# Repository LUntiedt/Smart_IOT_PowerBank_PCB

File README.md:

# Smart IoT Power Bank — Hardware (PD Edition)

A bidirectional USB-C Power Delivery (PD) power bank built around a software-defined PD stack and an I²C buck-boost charger. This repository holds the **KiCad hardware design** (schematic, layout, BOM, fabrication outputs). The firmware lives in a separate repository.

> **Firmware:** [`smart-iot-power-bank-firmware`](#) 

---

<!-- ───────────────────────────────────────────────────────────── -->
<!-- PROJECT IMAGE — replace the placeholder below with a real photo -->
<!-- Suggested: top-down render or photo of the assembled PCB.       -->
<!-- Drop the file into docs/img/ and update the path.               -->
<!-- ───────────────────────────────────────────────────────────── -->

<p align="center">
  
  <br>
  <em>Smart IoT Power Bank</em>
</p>

---

## 1. Overview

The board implements a professional power-management architecture comparable to those found in modern laptops. The same USB-C port handles **input (sink)** and **output (source/OTG)**, limited to a robust **30 W**. Energetic characterization (V/I telemetry, efficiency) is done entirely with the **internal 16-bit ADCs of the charge controller**, avoiding external sense amplifiers.

| Property | Value |
| :--- | :--- |
| Topology | Bidirectional USB-C PD (sink + source) |
| Battery | 4S1P Li-ion, 14.8 V nominal (~45 Wh) with integrated protection BMS |
| Max power | 30 W (5 V / 9 V / 12 V / 15 V / 20 V profiles) |
| MCU | ESP32-C3 (Wi-Fi/BLE) |
| Charger | TI BQ25792 I²C buck-boost |
| PD PHY | onsemi FUSB302B |
| Logic rail | TPS54202 buck → 3.3 V |
| EDA tool | KiCad |
| Fab house | [Aisler](https://aisler.net) (stackup & design rules tuned to Aisler) |

---

## 2. Hardware Architecture

### A. Power Path & USB-C Communication

| Designator | Part | Function | System Role |
| :--- | :--- | :--- | :--- |
| **U3** | `BQ25792RQMR` (TI) | I²C buck-boost charger | Handles charging (buck) and discharging (OTG/boost) in hardware. Single inductor L1 (2.2 µH). |
| **U1** | `FUSB302B11MPX` (onsemi) | USB Type-C PD PHY | Monitors the CC pins and translates PD signalling into I²C messages for the MCU. |
| **U6** | `TPS54202HDDCR` (TI) | 2 A step-down | Generates a clean **3.3 V** logic rail from the fluctuating system voltage. Inductor L2 (10 µH). |
| **Q1, Q2** | `CSD17581Q3A` (TI) | Dual N-channel MOSFETs | Back-to-back FETs for **reverse-polarity protection** / VBUS load isolation; block reverse current from the USB port into the system. |
| **J2** | Würth WR-MPC4 `64900311122` | Battery connector | Connects the external **4S1P 18650 pack** (14.8 V, ~45 Wh, with internal BMS). |

### B. Protection (TVS / ESD / Clamps)

| Designator | Part | Function | Notes |
| :--- | :--- | :--- | :--- |
| **U2, U4** | `TVS2200DRVR` (TI) | Flat-clamp surge protection | **VBUS TVS** — tight clamping on the high-current bus. |
| **D2, D4** | `TPD4E05U06DQAR` (TI) | 4-channel low-cap ESD | Protects **CC lines and the differential pairs** without loading the high-speed signals. |
| **D1** | `ZLLS350` (Diodes Inc.) | 40 V Schottky | Power-path / bootstrap diode. |
| **Z1** | `MMSZ5242B` | 12 V Zener | Rail clamp. |

### C. Sensing & Intelligence (IoT layer)

| Designator | Part | Function | Engineering benefit |
| :--- | :--- | :--- | :--- |
| **U5** | `ESP32-C3-WROOM-02-H4` (Espressif) | Master MCU | FSM control, software PD stack, I²C master, BLE server. |
| — | BQ25792 (internal) | 16-bit ADC telemetry | Reads V_BUS, I_BUS, V_BAT, I_BAT from the charger — no external current sensors. |
| **(TS pin)** | 10 k NTC | Thermistor | Cell temperature monitoring via the BQ25792 TS pin. |
| **J5** | 1×04 header | OLED / I²C | 0.96" OLED for local PD-profile and efficiency readout. |

### D. Connectors, Switches, Indicators

| Designator | Part | Function |
| :--- | :--- | :--- |
| **J1, J3** | USB-C receptacle (Würth `629722000214`) | Two USB-C ports — see differential-pair routing below. |
| **J4** | 2×03 header | Programming / debug header. |
| **SW1, SW2** | Würth tactile `434121025816` | Boot / reset buttons. |
| **D3** | Green LED (Würth) | Status indication. |

> Full part list with manufacturer numbers, footprints and datasheets: **[`ESP_Smart_IoT_Power_Bank.csv`](ESP_Smart_IoT_Power_Bank.csv)**.

---

## 3. Engineering Features & Physics

### I. Cascaded Power Supply (Logic Isolation)

To avoid system reboots under heavy load, the supply is cascaded:

1. **Primary stage** — the BQ25792 generates the system rail `V_SYS` from the 4S pack.
2. **Secondary stage** — a dedicated **TPS54202** bucks `V_SYS` down to a constant **3.3 V** for the logic. The ESP32 therefore always sees a clean rail, independent of current spikes in the power stage.

### II. Efficient 4S Power Routing (Buck & OTG)

The 4S pack (14.8 V) minimizes conversion losses:

* **Buck mode (sink):** at 20 V input the IC acts as an efficient step-down.
* **Buck/boost mode (source):** in OTG, 5 V / 9 V / 12 V are produced highly efficiently by buck conversion; only 20 V profiles (e.g. laptops) require a slight boost.

### III. Thermal & Electrical Derating

Thanks to the 4S configuration, PCB currents stay **below 3 A** even at 30 W:

```
I_bat_max = P_out / (U_bat · η)
I_bat_max = 30 W / (12.0 V · 0.9) ≈ 2.7 A   (worst case, empty pack)
```

On overheat (NTC > 60 °C) the ESP32 throttles PD power via software re-negotiation down to **5 W (5 V / 1 A)** as a fallback.

---

## 4. PCB Stackup & Layout

**4-layer board, built to Aisler's stackup and design rules.**

| Layer | Role |
| :--- | :--- |
| **Top** | Power / Signal |
| **Inner 1** | GND |
| **Inner 2** | GND |
| **Bottom** | Power / Signal |

The dual inner ground planes give the high-speed pairs a continuous reference and a low-impedance return for the power stage.

### Differential pairs

Two **impedance-controlled 90 Ω differential pairs** (USB 2.0 spec):

1. **USB power port (BQ25792):** backwards-compatible USB data for the power path.
2. **Debug/flash port (ESP32-C3):** USB used to flash and debug the MCU.

Both pairs are protected by the low-capacitance `TPD4E05U06` ESD arrays so the added capacitance does not degrade signal integrity.

### Layout guidelines

* **Ground partitioning** — clean ground concept separating the power stage (BQ25792) from the logic (ESP32 / TPS54202).
* **Copper polygons** — power paths (V_BUS, V_BAT, V_SYS) routed as filled polygons.
* **Thermal management** — implemented high power rails on both sides of the board to increase thermal capacity and placing a generous amount of vias to distribute current evenly

---

## 5. Design Decisions Log

* **Dual-MOSFET reverse-polarity protection** (Q1/Q2, CSD17581Q3A) instead of a single series diode — near-zero conduction loss on the power path.
* **VBUS TVS** (TVS2200) for surge clamping on the high-current bus.
* **Low-capacitance TVS/ESD** (TPD4E05U06) on CC lines and the differential pairs to preserve signal integrity.
* **Two 90 Ω impedance-controlled diff pairs:** one for backwards-compatible USB power data (BQ), one dedicated to flashing/debugging the MCU.
* **Aisler** chosen as fab house — the stackup and design rules in this project are tuned to Aisler's process.

---

## 6. Status

Hardware design in KiCad. See the firmware repository for the FreeRTOS PD stack.

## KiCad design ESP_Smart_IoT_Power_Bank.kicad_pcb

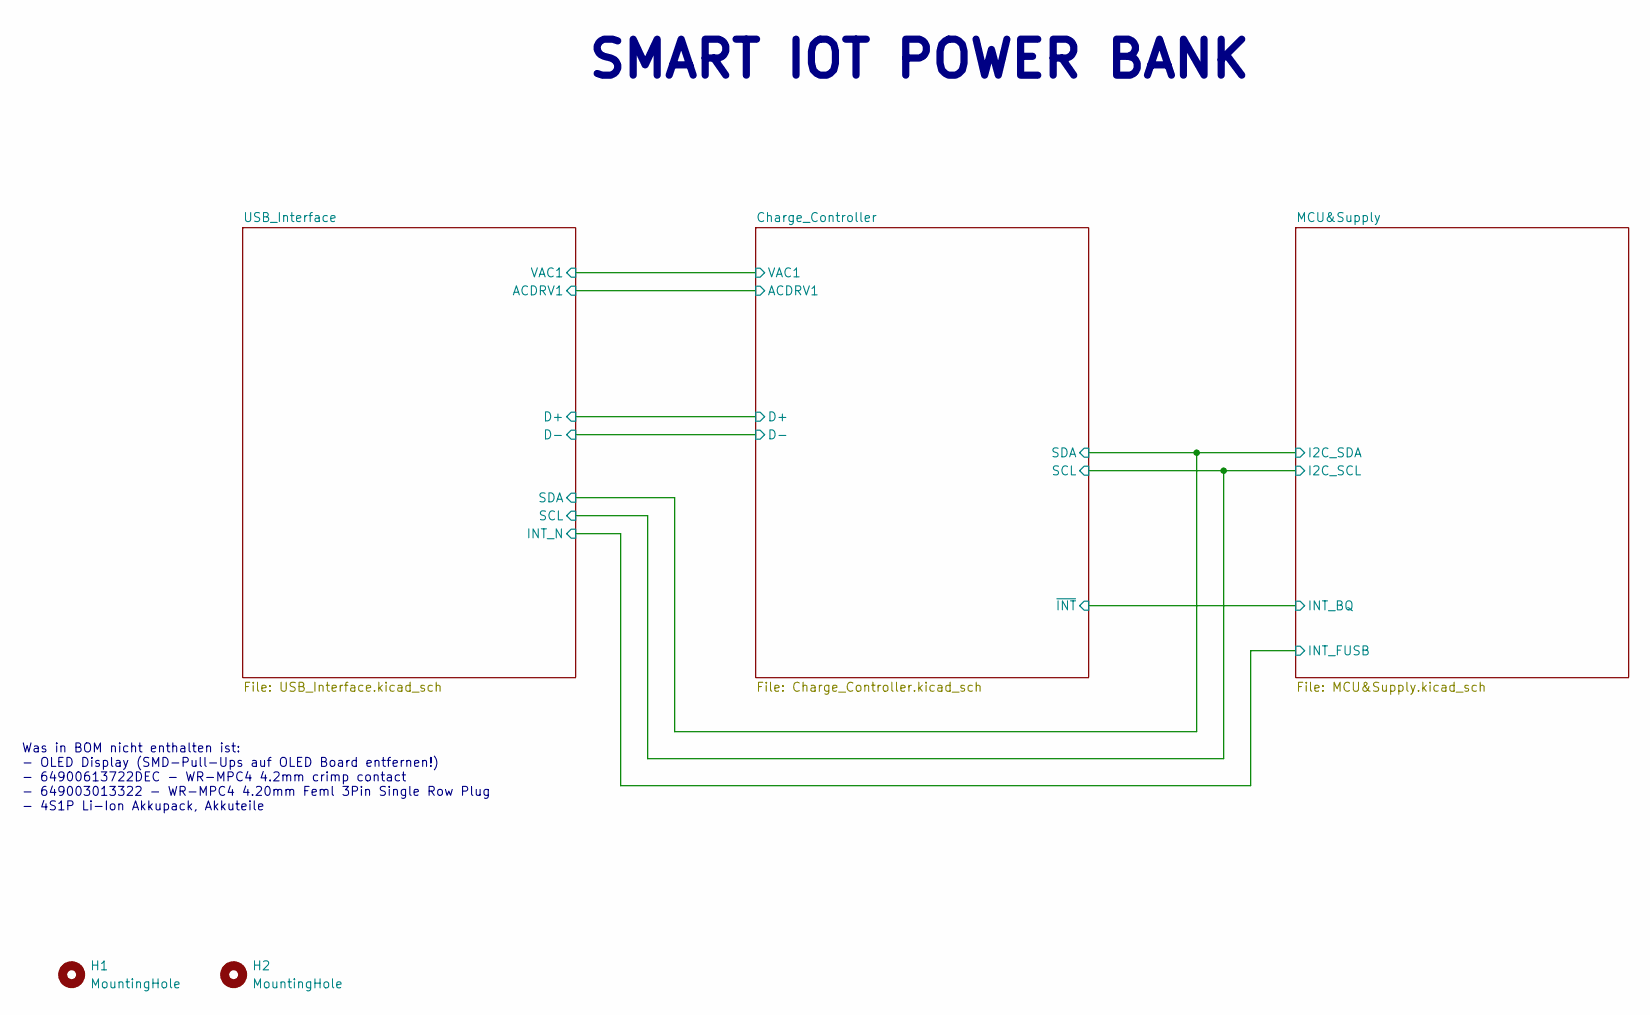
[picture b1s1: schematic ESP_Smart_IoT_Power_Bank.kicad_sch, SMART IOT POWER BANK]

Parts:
H1, H2: MountingHole; MountingHole_3.2mm_M3_ISO14580

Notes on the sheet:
SMART IOT POWER BANK
Was in BOM nicht enthalten ist: - OLED Display (SMD-Pull-Ups auf OLED Board entfernen!) - 64900613722DEC - WR-MPC4 4.2mm crimp contact - 649003013322 - WR-MPC4 4.20mm Feml 3Pin Single Row Plug - 4S1P Li-Ion Akkupack, Akkuteile

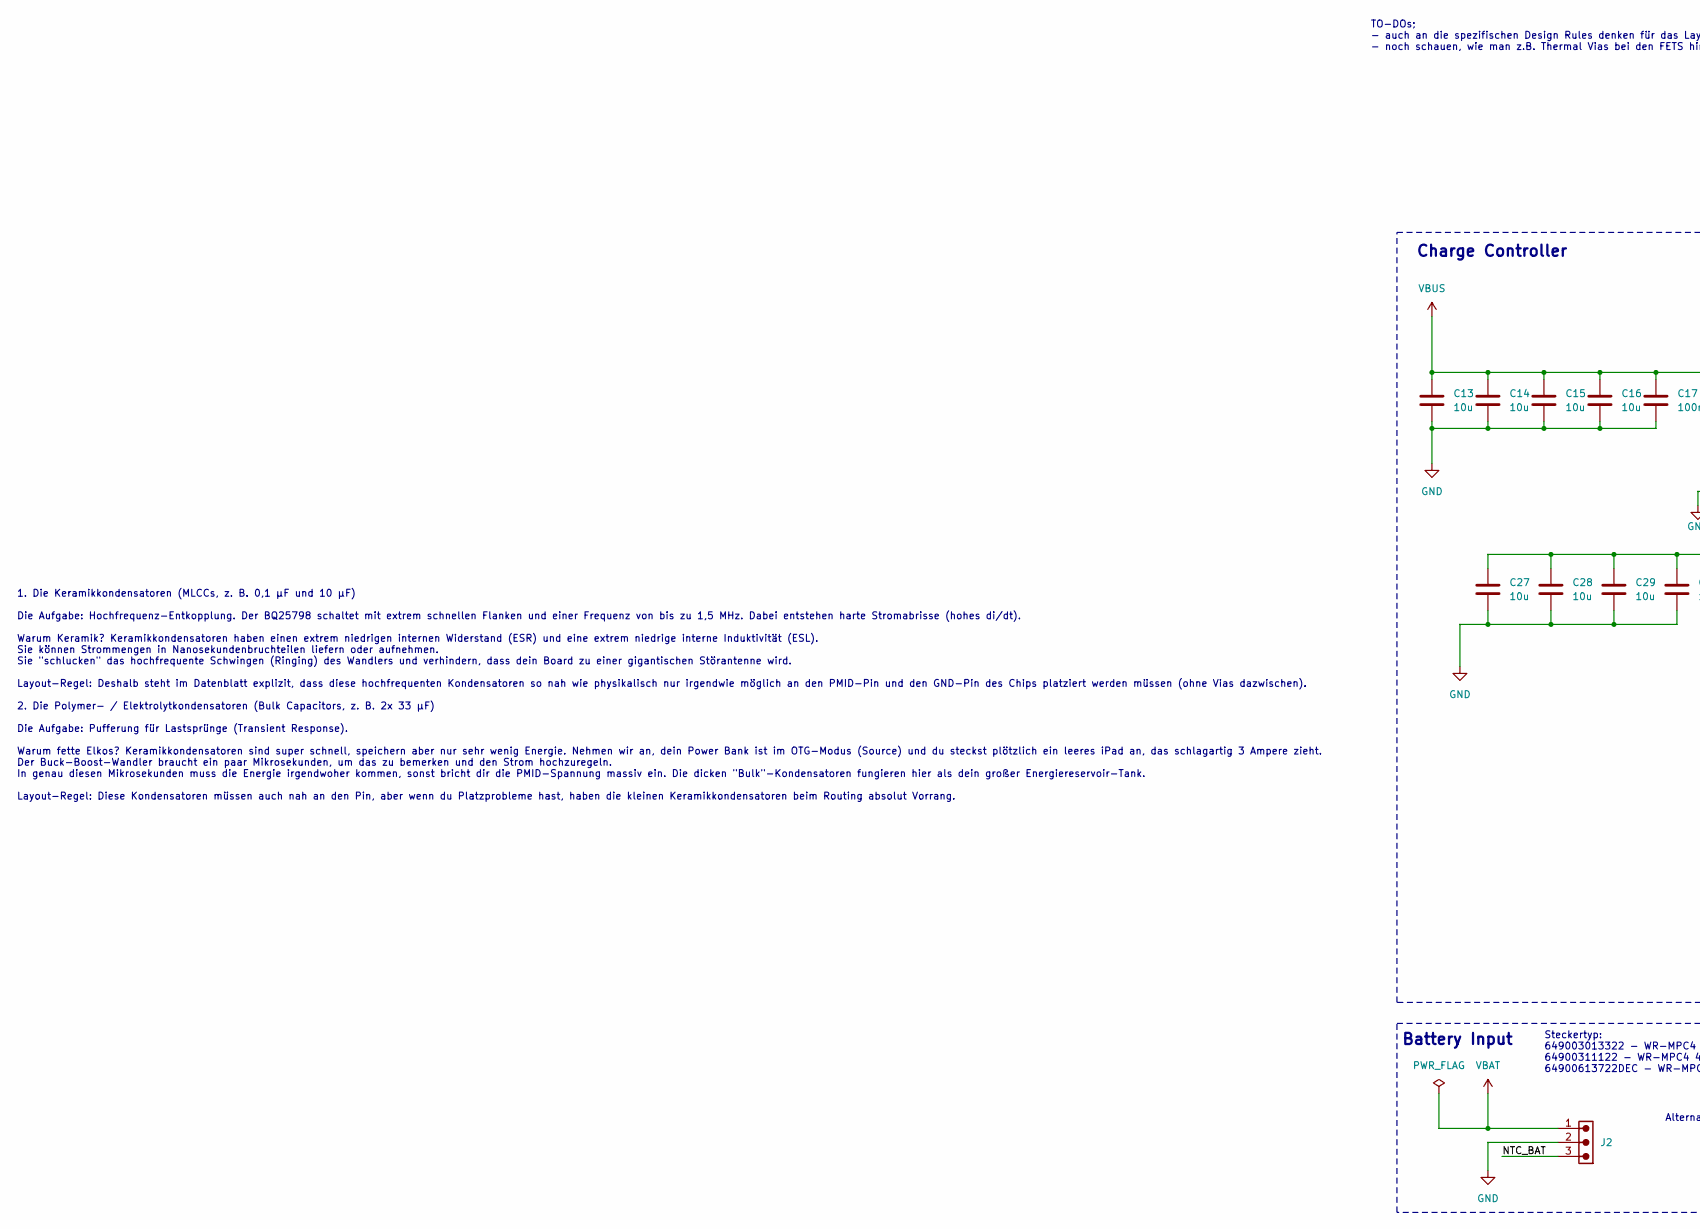
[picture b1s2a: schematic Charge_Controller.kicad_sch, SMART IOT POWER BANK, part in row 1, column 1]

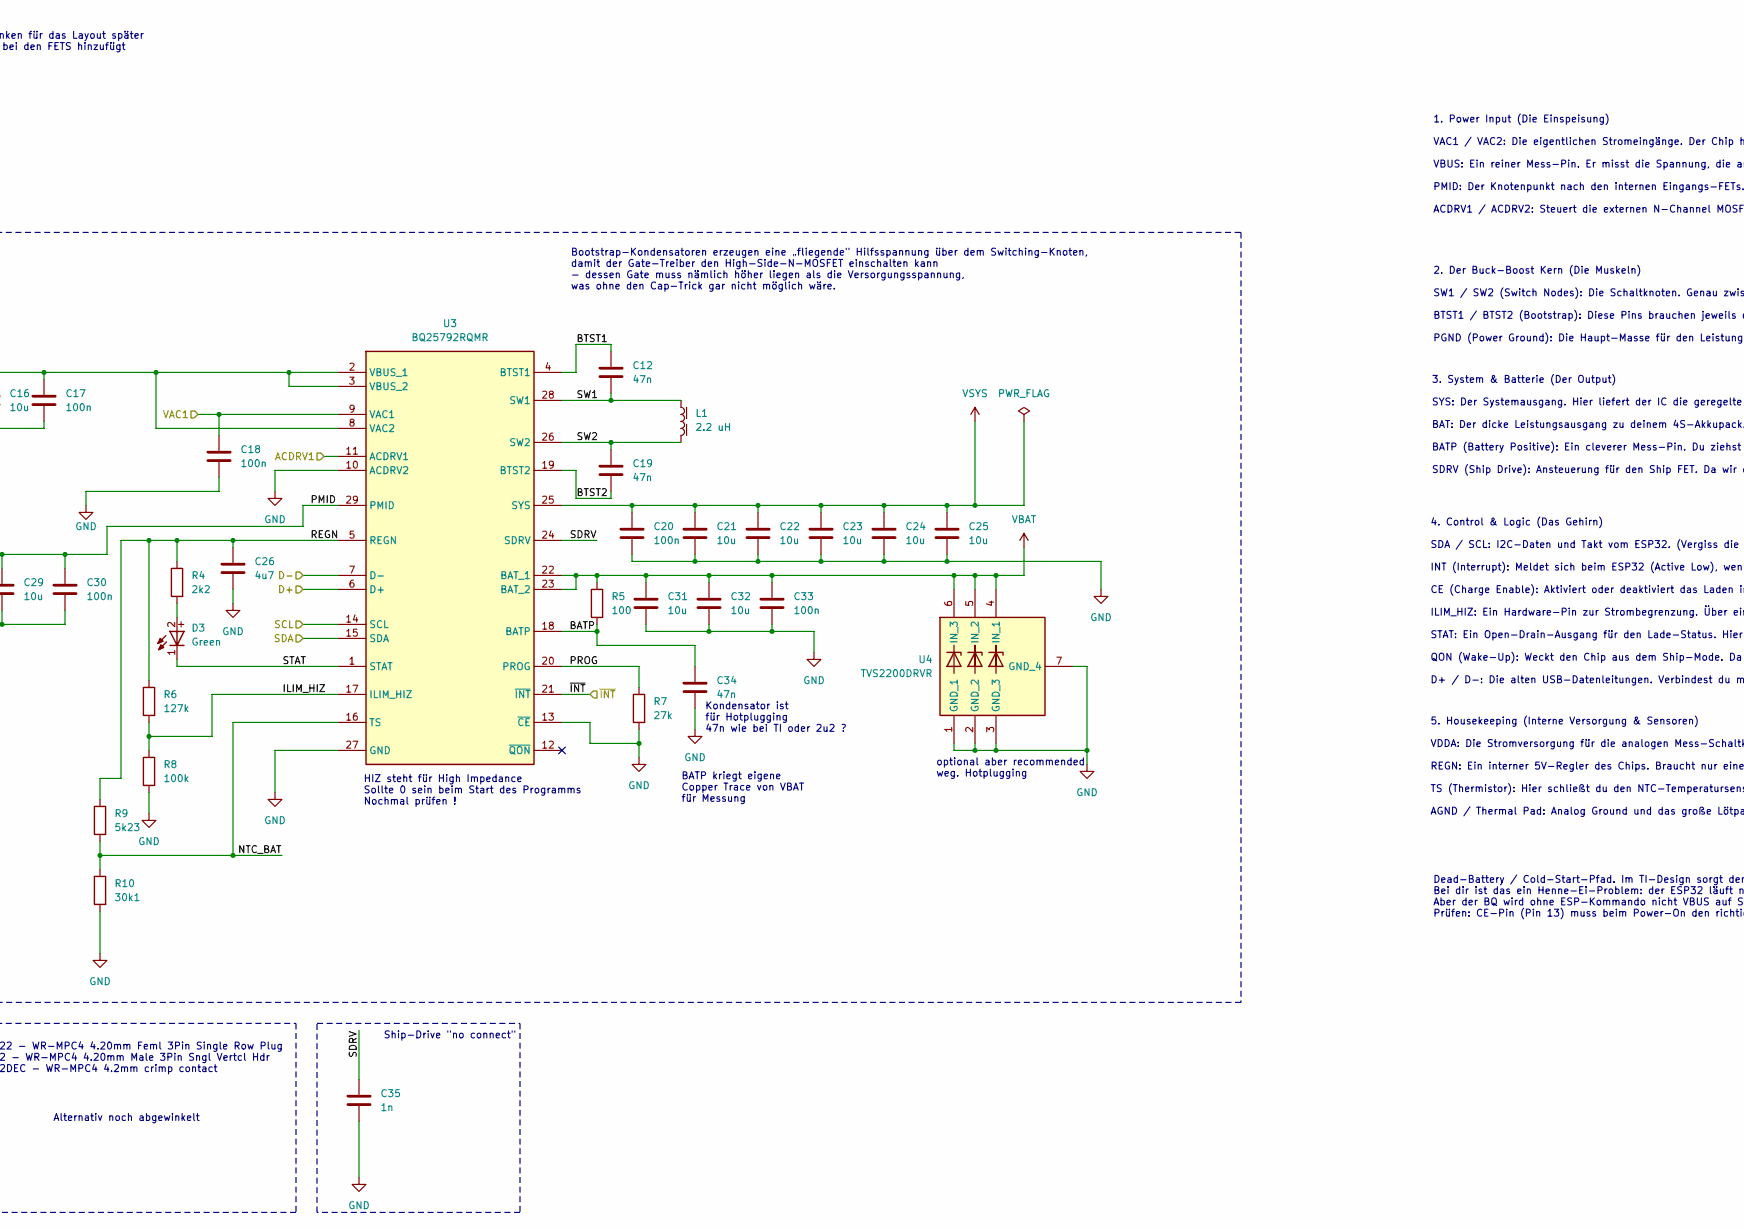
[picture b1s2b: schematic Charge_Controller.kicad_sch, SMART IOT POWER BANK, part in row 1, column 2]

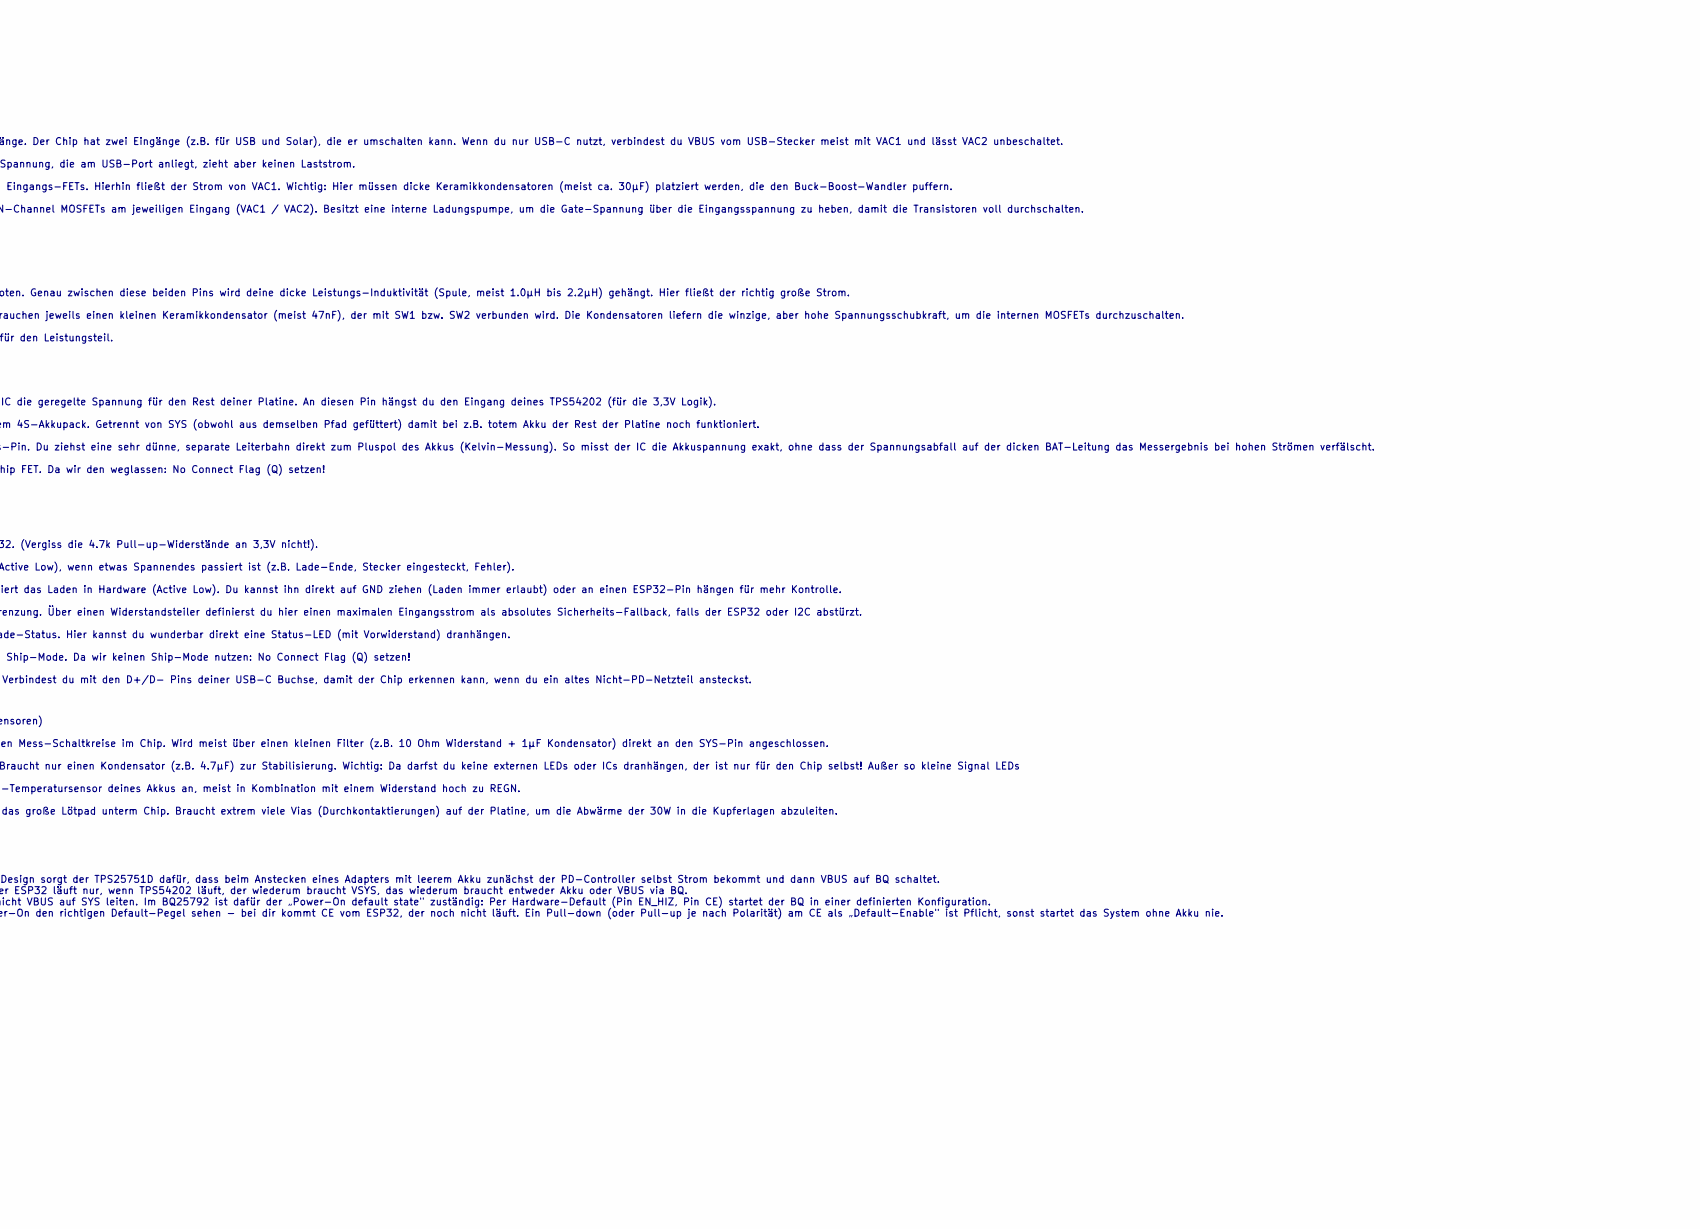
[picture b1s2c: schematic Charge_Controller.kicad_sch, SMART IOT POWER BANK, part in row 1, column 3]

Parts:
C12, C19: 47n; C_Wurth_WCAP-CSGP-0402; Voltage 25.0; Manufacturer_Part_Number 885012205054
C13, C14, C15, C16, C21, C22, C23, C24, C25, C27, C28, C29, C31, C32: 10u; C_Wurth_WCAP-CSGP-1206_H1.6; Voltage 25.0; Part Number 885012208069
C17, C18, C20, C30, C33: 100n; C_Wurth_WCAP-CSGP-0402; Voltage 50.0; Part Number 885012205086
C26: 4u7; C_Wurth_WCAP-CSGP-1206_H1.6; Voltage 25.0; Part Number 885012208068
C34: 47n; C_Wurth_WCAP-CSGP-0603_R; Voltage 50.0; Part Number 885012206093
C35: 1n; C_Wurth_WCAP-CSGP-0402; Voltage 50.0; Part Number 885012205061
D3: Green; D_Wurth_WL-SMCW-0603; Part Number 150060VS75000
J2: 64900311122; J_Wurth_WR-MPC4_64900311122; Working Voltage (V (AC)) 600; Manufacturer_Part_Number 64900311122
L1: 2.2 uH; L_Wurth_WE-LHMI-7030; Part Number 74437346022
R4: 2k2; R_Wurth_WRIS-RSKS-0402; Part Number 560112110087
R5: 100; R_Wurth_WRIS-RSKS-0402; Part Number 560112110022
R6: 127k; R_Wurth_WRIS-RSKS-0402; Part Number 560112110195
R7: 27k; R_Wurth_WRIS-RSKS-0402; Part Number 560112110026
R8: 100k; R_Wurth_WRIS-RSKS-0402; Part Number 560112110019
R9: 5k23; R_Wurth_WRIS-RSKS-0402; Manufacturer_Part_Number ERJ-U02D5231X
R10: 30k1; R_Wurth_WRIS-RSKS-0402; Mouser Part Number 667-ERJ-2RHD3012X
U3: BQ25792RQMR; Mouser Part Number 595-BQ25792RQMR
U4: TVS2200DRVR; SON65P200X200X80-7N; Mouser Part Number 595-TVS2200DRVR

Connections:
/Charge_Controller/ACDRV1: U3.11 (ACDRV1); also elsewhere on the board
/Charge_Controller/BATP: C34.1, R5.1, U3.18 (BATP)
/Charge_Controller/BTST1: C12.1, U3.4 (BTST1)
/Charge_Controller/BTST2: C19.2, U3.19 (BTST2)
/Charge_Controller/D+: U3.6 (D+); also elsewhere on the board
/Charge_Controller/D-: U3.7 (D-); also elsewhere on the board
/Charge_Controller/ILIM_HIZ: R6.1, R8.2, U3.17 (ILIM_HIZ)
/Charge_Controller/NTC_BAT: J2.3, R9.1, R10.2, U3.16 (TS)
/Charge_Controller/PMID: C27.1, C28.1, C29.1, C30.1, U3.29 (PMID)
/Charge_Controller/PROG: R7.2, U3.20 (PROG)
/Charge_Controller/REGN: C26.1, R4.2, R6.2, R9.2, U3.5 (REGN)
/Charge_Controller/SDRV: C35.1, U3.24 (SDRV)
/Charge_Controller/STAT: D3.1 (-), U3.1 (STAT)
/Charge_Controller/SW1: C12.2, L1.1, U3.28 (SW1)
/Charge_Controller/SW2: C19.1, L1.2, U3.26 (SW2)
/Charge_Controller/~INT: U3.21 (~INT); also elsewhere on the board
/MCU&Supply/I2C_SCL: U3.14 (SCL); also elsewhere on the board
/MCU&Supply/I2C_SDA: U3.15 (SDA); also elsewhere on the board
/USB_Interface/VBUS_RAW: C18.1, U3.9 (VAC1); also elsewhere on the board
GND: C13.2, C14.2, C15.2, C16.2, C17.2, C18.2, C20.2, C21.2, C22.2, C23.2, C24.2, C25.2, C26.2, C27.2, C28.2, C29.2, C30.2, C31.2, C32.2, C33.2, C34.2, C35.2, J2.2, R7.1, R8.1, R10.1, U3.10 (ACDRV2), U3.13 (~CE), U3.27 (GND), U4.1 (GND_1), U4.2 (GND_2), U4.3 (GND_3), U4.7 (GND_4); also elsewhere on the board
unnamed: D3.2 (+), R4.1
VBAT: C31.1, C32.1, C33.1, J2.1, R5.2, U3.22 (BAT_1), U3.23 (BAT_2), U4.4 (IN_1), U4.5 (IN_2), U4.6 (IN_3)
VBUS: C13.1, C14.1, C15.1, C16.1, C17.1, U3.2 (VBUS_1), U3.3 (VBUS_2), U3.8 (VAC2); also elsewhere on the board
VSYS: C20.1, C21.1, C22.1, C23.1, C24.1, C25.1, U3.25 (SYS); also elsewhere on the board

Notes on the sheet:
3. System & Batterie (Der Output) SYS: Der Systemausgang. Hier liefert der IC die geregelte Spannung für den Rest deiner Platine. An diesen Pin hängst du den Eingang deines TPS54202 (für die 3,3V Logik). BAT: Der dicke Leistungsausgang zu deinem 4S-Akkupack. Getrennt von SYS (obwohl aus demselben P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
1. Die Keramikkondensatoren (MLCCs, z. B. 0,1 µF und 10 µF) Die Aufgabe: Hochfrequenz-Entkopplung. Der BQ25798 schaltet mit extrem schnellen Flanken und einer Frequenz von bis zu 1,5 MHz. Dabei entstehen harte Stromabrisse (hohes di/dt). Warum Keramik? Keramikkondensatoren haben einen extrem niedri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
1. Power Input (Die Einspeisung) VAC1 / VAC2: Die eigentlichen Stromeingänge. Der Chip hat zwei Eingänge (z.B. für USB und Solar), die er umschalten kann. Wenn du nur USB-C nutzt, verbindest du VBUS vom USB-Stecker meist mit VAC1 und lässt VAC2 unbeschaltet. VBUS: Ein reiner Mess-Pin. Er misst die 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
2. Der Buck-Boost Kern (Die Muskeln) SW1 / SW2 (Switch Nodes): Die Schaltknoten. Genau zwischen diese beiden Pins wird deine dicke Leistungs-Induktivität (Spule, meist 1.0µH bis 2.2µH) gehängt. Hier fließt der richtig große Strom. BTST1 / BTST2 (Bootstrap): Diese Pins brauchen jeweils einen kleinen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
Bootstrap-Kondensatoren erzeugen eine „fliegende" Hilfsspannung über dem Switching-Knoten, damit der Gate-Treiber den High-Side-N-MOSFET einschalten kann - dessen Gate muss nämlich höher liegen als die Versorgungsspannung, was ohne den Cap-Trick gar nicht möglich wäre.
Charge Controller
Battery Input
HIZ steht für High Impedance Sollte 0 sein beim Start des Programms Nochmal prüfen !
Kondensator ist für Hotplugging 47n wie bei TI oder 2u2 ?
Ship-Drive "no connect"
Steckertyp: 649003013322 - WR-MPC4 4.20mm Feml 3Pin Single Row Plug 64900311122 - WR-MPC4 4.20mm Male 3Pin Sngl Vertcl Hdr 64900613722DEC - WR-MPC4 4.2mm crimp contact
BATP kriegt eigene Copper Trace von VBAT für Messung
TO-DOs; - auch an die spezifischen Design Rules denken für das Layout später - noch schauen, wie man z.B. Thermal Vias bei den FETS hinzufügt
optional aber recommended weg. Hotplugging
4. Control & Logic (Das Gehirn) SDA / SCL: I2C-Daten und Takt vom ESP32. (Vergiss die 4.7k Pull-up-Widerstände an 3,3V nicht!). INT (Interrupt): Meldet sich beim ESP32 (Active Low), wenn etwas Spannendes passiert ist (z.B. Lade-Ende, Stecker eingesteckt, Fehler). CE (Charge Enable): Aktiviert oder 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
5. Housekeeping (Interne Versorgung & Sensoren) VDDA: Die Stromversorgung für die analogen Mess-Schaltkreise im Chip. Wird meist über einen kleinen Filter (z.B. 10 Ohm Widerstand + 1µF Kondensator) direkt an den SYS-Pin angeschlossen. REGN: Ein interner 5V-Regler des Chips. Braucht nur einen Konden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
Dead-Battery / Cold-Start-Pfad. Im TI-Design sorgt der TPS25751D dafür, dass beim Anstecken eines Adapters mit leerem Akku zunächst der PD-Controller selbst Strom bekommt und dann VBUS auf BQ schaltet. Bei dir ist das ein Henne-Ei-Problem: der ESP32 läuft nur, wenn TPS54202 läuft, der wiederum brau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
Alternativ noch abgewinkelt

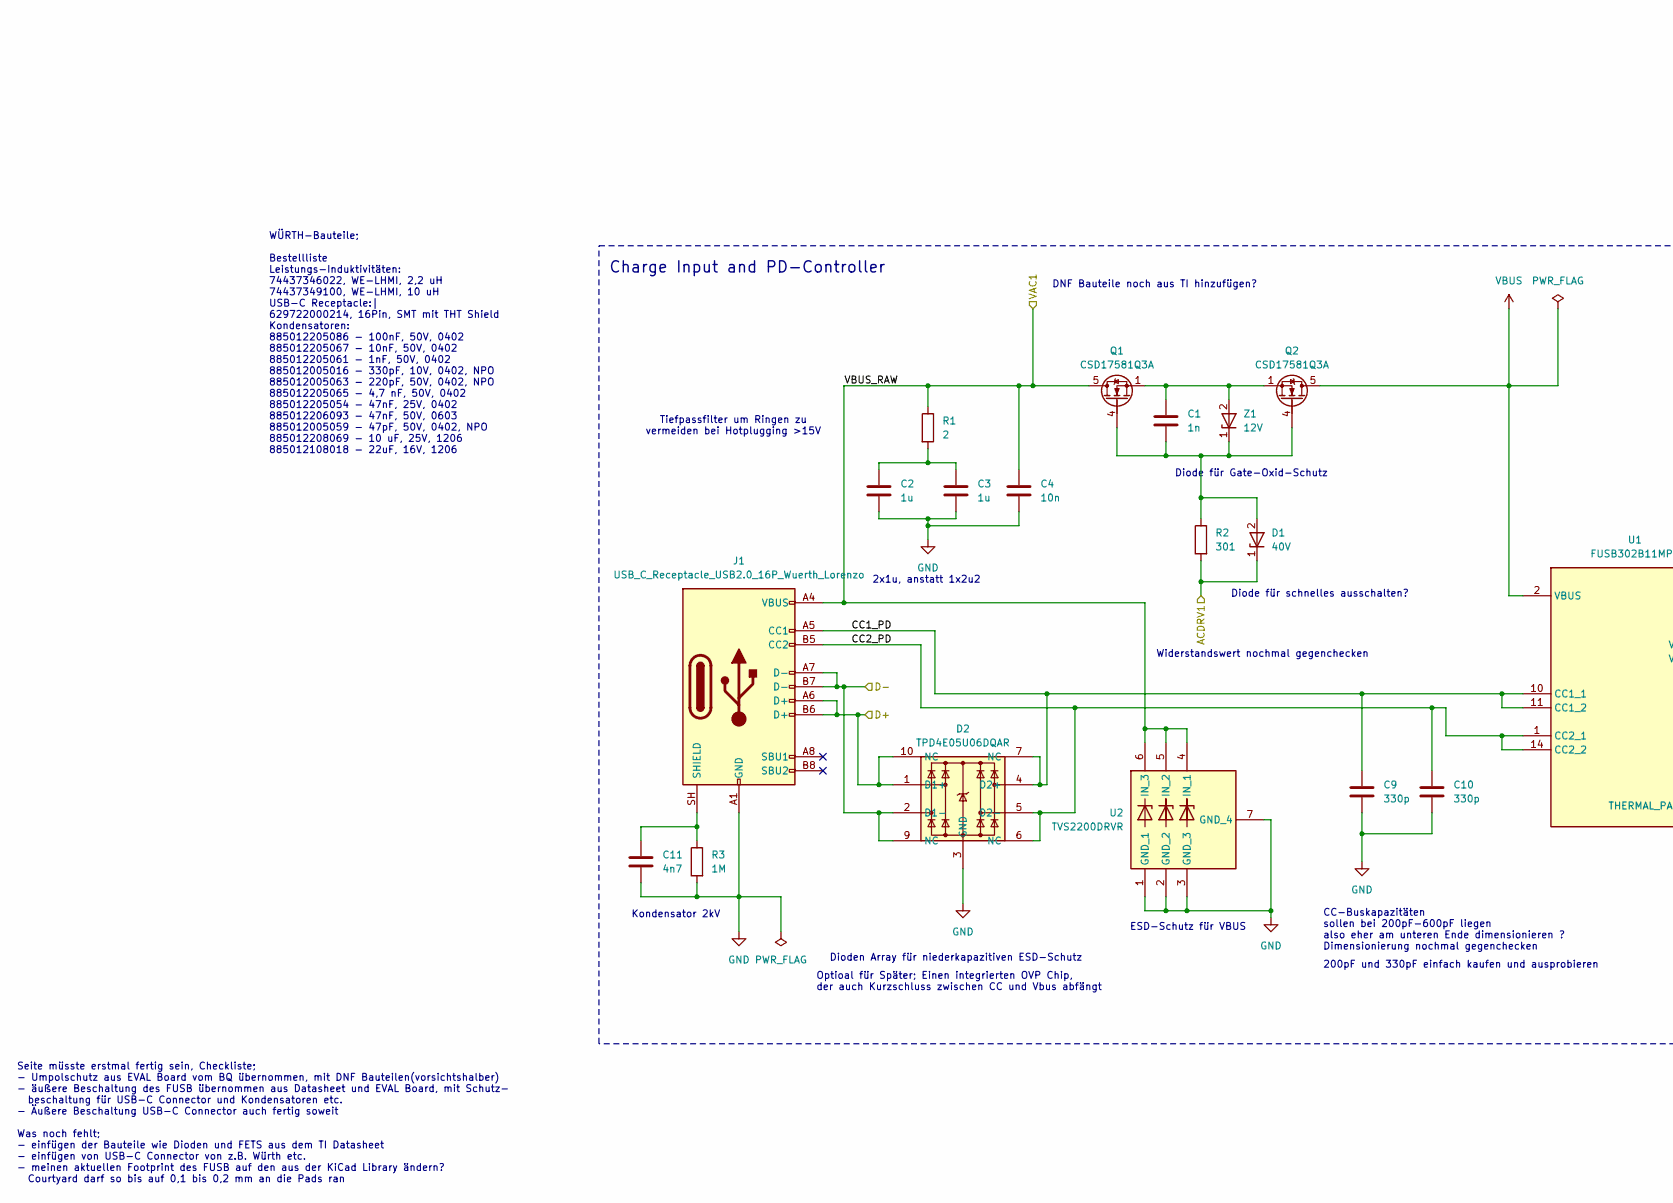
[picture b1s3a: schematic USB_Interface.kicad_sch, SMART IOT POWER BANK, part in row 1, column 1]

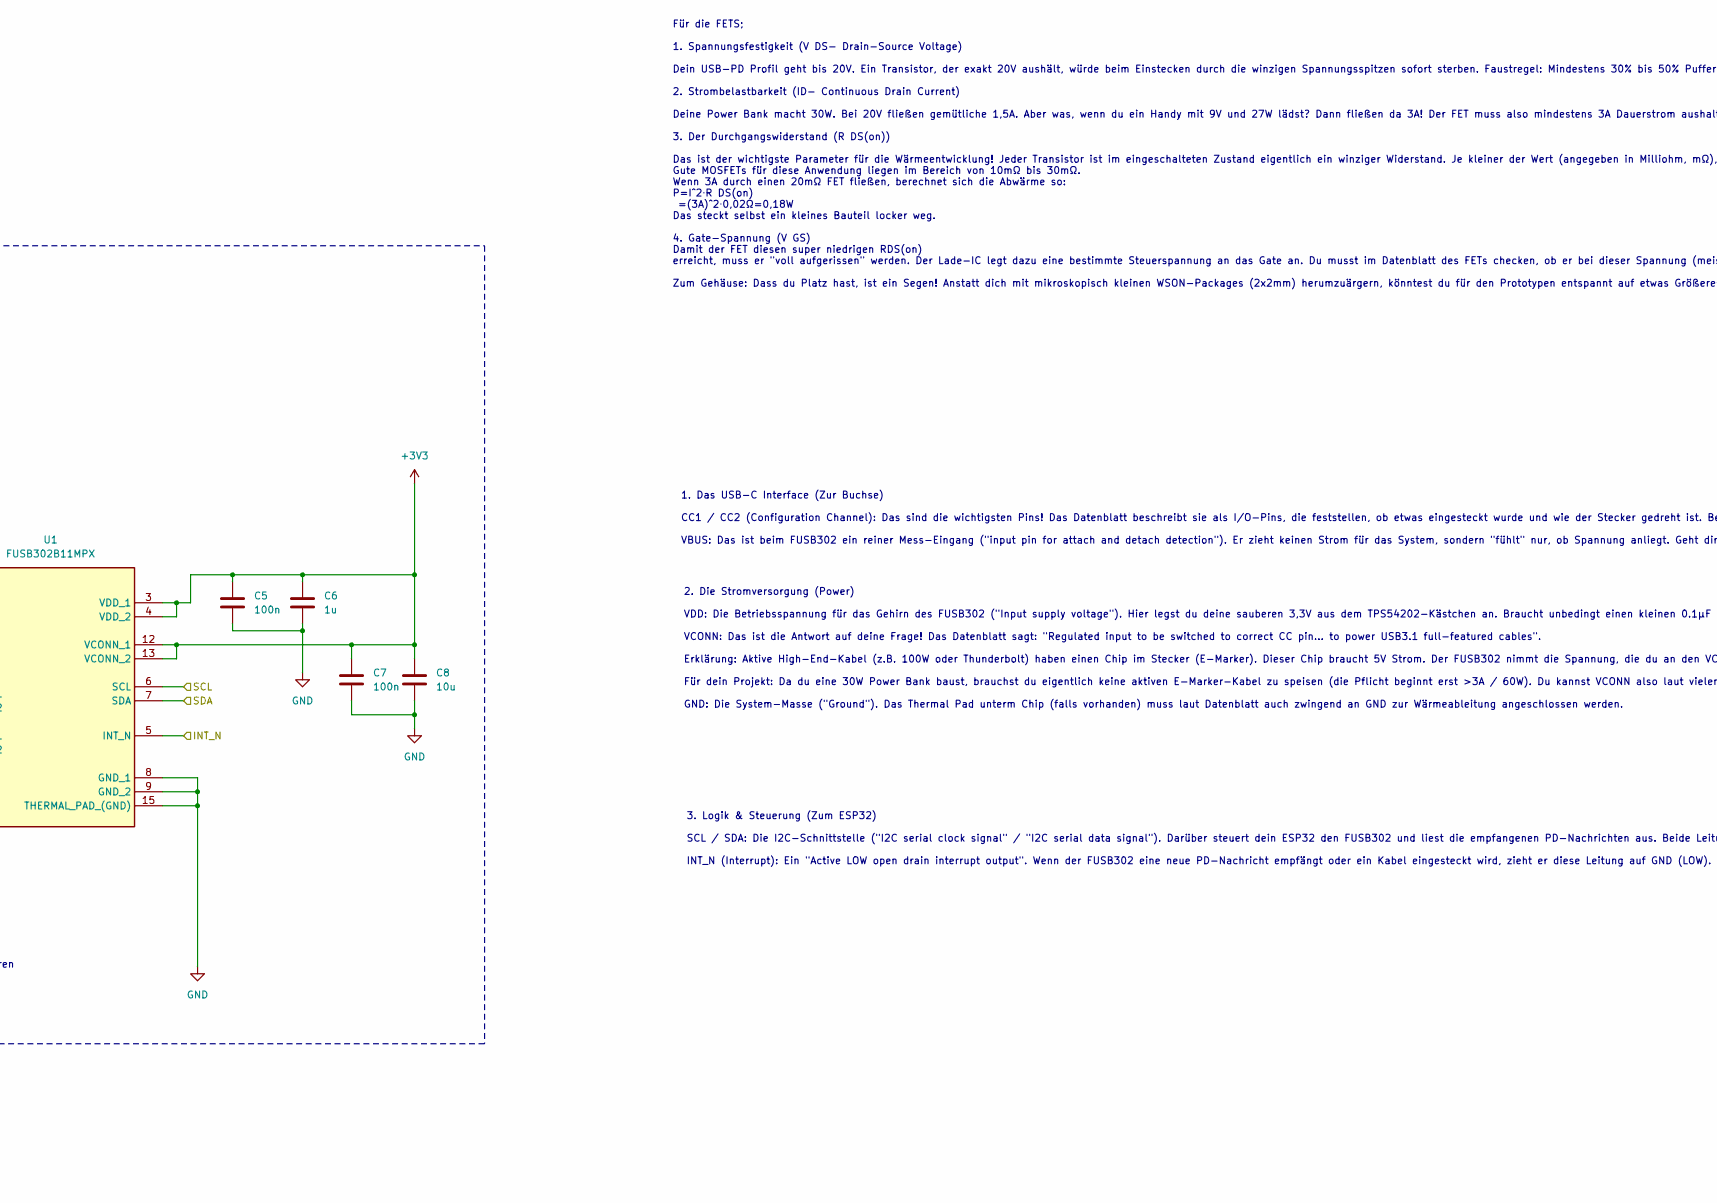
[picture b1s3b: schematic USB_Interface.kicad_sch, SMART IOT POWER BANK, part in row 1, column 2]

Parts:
C1: 1n; C_Wurth_WCAP-CSGP-0402; Voltage 50.0; Part Number 885012205061
C2, C3, C6: 1u; C_Wurth_WCAP-CSGP-1206_H1.6; Voltage 50.0; Part Number 885012208093
C4: 10n; C_Wurth_WCAP-CSGP-0402; Voltage 50.0; Part Number 885012205067
C5, C7: 100n; C_Wurth_WCAP-CSGP-0402; Voltage 50.0; Part Number 885012205086
C8: 10u; C_Wurth_WCAP-CSGP-1206_H1.6; Voltage 25.0; Part Number 885012208069
C9, C10: 330p; C_Wurth_WCAP-CSGP-0402; Voltage 10.0; Part Number 885012005016
C11: 4n7; C_Wurth_WCAP-CSGP-0402; Voltage 50.0; Part Number 885012205065
D1: 40V; SODFL1608X65N; Mouser Part Number 522-ZLLS350TA
D2: TPD4E05U06DQAR; DQA_R-PUSON-N10_; Mouser Part Number 595-TPD4E05U06DQAR
J1: USB_C_Receptacle_USB2.0_16P_Wuerth_Lorenzo; 629722000214; Manufacturer_Part_Number 629722000214
Q1, Q2: CSD17581Q3A; CSD17581Q3A_LorenzonF; Manufacturer_Part_Number CSD17581Q3A
R1: 2; R_Wurth_WRIS-RSKS-0402; Part Number 560112110057
R2: 301; R_Wurth_WRIS-RSKS-0402; Part Number 560112110092
R3: 1M; R_Wurth_WRIS-RSKS-0402; Part Number 560112110033
U1: FUSB302B11MPX; QFN50P250X250X80-15N; Mouser Part Number 512-FUSB302B11MPX
U2: TVS2200DRVR; SON65P200X200X80-7N; Mouser Part Number 595-TVS2200DRVR
Z1: 12V; SOD3716X145N; Mouser Part Number 621-MMSZ5242B-F

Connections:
+3V3: C5.1, C6.1, C7.1, C8.1, U1.3 (VDD_1), U1.4 (VDD_2), U1.12 (VCONN_1), U1.13 (VCONN_2); also elsewhere on the board
/Charge_Controller/ACDRV1: D1.1 (K), R2.1; also elsewhere on the board
/Charge_Controller/D+: D2.1 (D1+), D2.10 (NC), J1.A6 (D+), J1.B6 (D+); also elsewhere on the board
/Charge_Controller/D-: D2.2 (D1-), D2.9 (NC), J1.A7 (D-), J1.B7 (D-); also elsewhere on the board
/MCU&Supply/I2C_SCL: U1.6 (SCL); also elsewhere on the board
/MCU&Supply/I2C_SDA: U1.7 (SDA); also elsewhere on the board
/MCU&Supply/INT_FUSB: U1.5 (INT_N); also elsewhere on the board
/USB_Interface/CC1_PD: C9.1, D2.4 (D2+), D2.7 (NC), J1.A5 (CC1), U1.10 (CC1_1), U1.11 (CC1_2)
/USB_Interface/CC2_PD: C10.1, D2.5 (D2-), D2.6 (NC), J1.B5 (CC2), U1.1 (CC2_1), U1.14 (CC2_2)
/USB_Interface/VBUS_RAW: C4.1, J1.A4 (VBUS), Q1.5 (D), R1.2, U2.4 (IN_1), U2.5 (IN_2), U2.6 (IN_3); also elsewhere on the board
GND: C2.2, C3.2, C4.2, C5.2, C6.2, C7.2, C8.2, C9.2, C10.2, C11.2, D2.3 (GND), D2.8 (GND), J1.A1 (GND), R3.1, U1.8 (GND_1), U1.9 (GND_2), U1.15 (THERMAL_PAD_(GND)), U2.1 (GND_1), U2.2 (GND_2), U2.3 (GND_3), U2.7 (GND_4); also elsewhere on the board
unnamed: C2.1, C3.1, R1.1
unnamed: C1.2, D1.2 (A), Q1.4 (G), Q2.4 (G), R2.2, Z1.1 (K)
unnamed: C11.1, J1.SH (SHIELD), R3.2
unnamed: C1.1, Q1.1 (S), Q1.2 (S), Q1.3 (S), Q2.1 (S), Q2.2 (S), Q2.3 (S), Z1.2 (A)
VBUS: Q2.5 (D), U1.2 (VBUS); also elsewhere on the board

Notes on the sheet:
1. Das USB-C Interface (Zur Buchse) CC1 / CC2 (Configuration Channel): Das sind die wichtigsten Pins! Das Datenblatt beschreibt sie als I/O-Pins, die feststellen, ob etwas eingesteckt wurde und wie der Stecker gedreht ist. Bei PD-Kommunikation senden und empfangen sie die eigentlichen Datenpakete (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
2. Die Stromversorgung (Power) VDD: Die Betriebsspannung für das Gehirn des FUSB302 ("Input supply voltage"). Hier legst du deine sauberen 3,3V aus dem TPS54202-Kästchen an. Braucht unbedingt einen kleinen 0.1µF (100nF) Entkoppelkondensator direkt am Pin nach GND! VCONN: Das ist die Antwort auf dei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
ESD-Schutz für VBUS
2x1u, anstatt 1x2u2
CC-Buskapazitäten sollen bei 200pF-600pF liegen also eher am unteren Ende dimensionieren ? Dimensionierung nochmal gegenchecken
Kondensator 2kV
Seite müsste erstmal fertig sein, Checkliste; - Umpolschutz aus EVAL Board vom BQ übernommen, mit DNF Bauteilen(vorsichtshalber) - äußere Beschaltung des FUSB übernommen aus Datasheet und EVAL Board, mit Schutz- beschaltung für USB-C Connector und Kondensatoren etc. - Äußere Beschaltung USB-C Conne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
Widerstandswert nochmal gegenchecken
Dioden Array für niederkapazitiven ESD-Schutz
Tiefpassfilter um Ringen zu vermeiden bei Hotplugging >15V
Diode für schnelles ausschalten?
Optioal für Später; Einen integrierten OVP Chip, der auch Kurzschluss zwischen CC und Vbus abfängt
Für die FETS; 1. Spannungsfestigkeit (V DS- Drain-Source Voltage) Dein USB-PD Profil geht bis 20V. Ein Transistor, der exakt 20V aushält, würde beim Einstecken durch die winzigen Spannungsspitzen sofort sterben. Faustregel: Mindestens 30% bis 50% Puffer. Du suchst also nach einem FET mit mindestens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
3. Logik & Steuerung (Zum ESP32) SCL / SDA: Die I2C-Schnittstelle ("I2C serial clock signal" / "I2C serial data signal"). Darüber steuert dein ESP32 den FUSB302 und liest die empfangenen PD-Nachrichten aus. Beide Leitungen brauchen einen Pull-up-Widerstand (meist 4.7kΩ) gegen 3,3V. INT_N (Interrupt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
Diode für Gate-Oxid-Schutz
Charge Input and PD-Controller
200pF und 330pF einfach kaufen und ausprobieren
WÜRTH-Bauteile; Bestellliste Leistungs-Induktivitäten: 74437346022, WE-LHMI, 2,2 uH 74437349100, WE-LHMI, 10 uH USB-C Receptacle:| 629722000214, 16Pin, SMT mit THT Shield Kondensatoren: 885012205086 - 100nF, 50V, 0402 885012205067 - 10nF, 50V, 0402 885012205061 - 1nF, 50V, 0402 885012005016 - 330pF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
DNF Bauteile noch aus TI hinzufügen?
